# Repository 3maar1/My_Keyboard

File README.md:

# 3maar's Keyboard.
an RGB custom mechanical keyboard with an OLED screen and some custom features.
I made this project because i always wanted to make my stuff by myself and have my name signed on it.

## Custom features:
- signed my name behind
- some sk6812 for better colors since my keyboard is all black.
- an oled screen to give a pretty look 
- some holders from inside the case to ensure having the stability for the PCB.
- and i'm planning to add some of the hack club stickers on the left space when printed.

### -The Schematic
I used kicad with scottokeebs library and wired everything in the schematic. wired some LEDs with each other, the voltage supply and the ground. then made the switches matrix with diodes. it was the simplest thing in this project.

### -The PCB
I used a KLE plugin to arrange the switches and diodes, and manually put the led and the oled. and routed everything together. that was hard a bit but it's done.

### -The 3d Model
I made the 3d model using fusion and added some custom features like signing my name on the back. and made the holes for the socket and the oled. the model is separated to a plate, case, bottom and the pcb inside as a reference. made them all black and designed them to fit together.

### -BOM
this is all the components with their prices and sources
| Item                                     | Price (USD) | Link                                                                                                                                                                                                                                                                                                                                                                                                                                                                                                                                                                                                                                                                                                                                                                                                                                                                                                                |
|------------------------------------------|-------------|---------------------------------------------------------------------------------------------------------------------------------------------------------------------------------------------------------------------------------------------------------------------------------------------------------------------------------------------------------------------------------------------------------------------------------------------------------------------------------------------------------------------------------------------------------------------------------------------------------------------------------------------------------------------------------------------------------------------------------------------------------------------------------------------------------------------------------------------------------------------------------------------------------------------|
| Raspberry Pi Pico                        | 10.27$      | https://mostelectronic.com/shop/arduino-development-boards/raspberry-pi/raspberry-pi-pico/                                                                                                                                                                                                                                                                                                                                                                                                                                                                                                                                                                                                                                                                                                                                                                                                                          |
| Diodes                                   | 0.63$       | https://mostelectronic.com/shop/components/diodes/zener-diode-bzx79-c5v1-6-2-volt/                                                                                                                                                                                                                                                                                                                                                                                                                                                                                                                                                                                                                                                                                                                                                                                                                                  |
| Keyswitches                              | 32.88$      | https://www.amazon.eg/gp/product/B09QGQVQYD/ref=ewc_pr_img_1?smid=A1ZVRGNO5AYLOV&psc=1                                                                                                                                                                                                                                                                                                                                                                                                                                                                                                                                                                                                                                                                                                                                                                                                                              |
| OLED Display 128x64 0.9 Inches           | 3.29$       | https://mostelectronic.com/shop/displays-lcd-7-seg-led/lcd-modules-displays-lcd-7-seg-led/0-96%e2%80%b3-oled-4pin-lcd-led-display-module-i2c-iic-communicate-white-128x64/                                                                                                                                                                                                                                                                                                                                                                                                                                                                                                                                                                                                                                                                                                                                          |
| Keycaps                                  | 7.8$        | https://www.amazon.eg/A101-%D8%B1%D9%8A%D8%AF%D8%B1%D8%A7%D8%AC%D9%88%D9%86-%D8%A7%D9%84%D9%85%D9%81%D8%A7%D8%AA%D9%8A%D8%AD-%D9%84%D9%84%D9%83%D9%8A%D8%A8%D9%88%D8%B1%D8%AF%D8%A7%D8%AA-%D8%A7%D9%84%D9%85%D9%8A%D9%83%D8%A7%D9%86%D9%8A%D9%83%D9%8A%D8%A9/dp/B019OAQ6VI/ref=sr_1_1?crid=131S63DNWPQR6&dib=eyJ2IjoiMSJ9.zIUjY2wUg3Nr9eWWHxwMfdlZPoJ82SGaTR_8OmixACQynGSJOojGDpKWlqtbs5IB6GCVc1rAfDB6EvpbigCdmxsXlxrynCch2fziUpjr7793tyFKOseA_WWf__-g5L1vRob5zpO2BCE7vJej3N2mrVzUkW2OvBvp_q3Jx5KZeFjjB1dGx8bEQDQCwY4ly9DfJHsu265k53HfGW_IibxRO0eW2tv6JjcYAqhP_g4G8SHVFaU4gUwuFmVsNDeqDbZmk1LCvg4wyF9-t-nXhXivgySMUWYcV6g9IOC3sEq67Vg.JFwf40Zm6aGwKnDikG4YgNpKN-pXz8NDLLdcygQKYl0&dib_tag=se&keywords=black%2Bkeycaps&qid=1753918745&sprefix=black%2Bkeycaps%2Caps%2C177&sr=8-1&th=1                                                                                                                                |
| Solderig Wire                            | 1.54$       | https://mostelectronic.com/shop/tools/soldering-desoldering/solder-wire-singapore-25g-0-6mm-70-30-singapore/                                                                                                                                                                                                                                                                                                                                                                                                                                                                                                                                                                                                                                                                                                                                                                                                        |
| Soldering Iron Tips                      | 1.34$       | https://mostelectronic.com/shop/tools/soldering-desoldering/soldering-iron-station-tips-5pcs/                                                                                                                                                                                                                                                                                                                                                                                                                                                                                                                                                                                                                                                                                                                                                                                                                       |
| ""Most Electronics""  shop shipping fees | 1.54$       | Raspberry Pi Pico + Diodes + OLED Display + Soldering Wire + Soldering Iron Tips                                                                                                                                                                                                                                                                                                                                                                                                                                                                                                                                                                                                                                                                                                                                                                                                                                    |
| ""Amazon"" shipping fees                 | Free        | Keyswitches + Keycaps                                                                                                                                                                                                                                                                                                                                                                                                                                                                                                                                                                                                                                                                                                                                                                                                                                                                                               |
| ""JLCPCB"" Printing with shipping fees   | 18.20$      | PCB printing                                                                                                                                                                                                                                                                                                                                                                                                                                                                                                                                                                                                                                                                                                                                                                                                                                                                                                        |
| Glue                                     | 2.88$       | https://www.amazon.eg/%D9%85%D8%AA%D8%B9%D8%AF%D8%AF-%D8%A7%D9%84%D8%A7%D8%B3%D8%AA%D8%AE%D8%AF%D8%A7%D9%85%D8%A7%D8%AA-%D9%85%D9%88%D8%AF%D9%8A%D9%84-%D8%A7%D9%83%D9%81%D9%8A%D9%83%D8%B3%D8%8C-200/dp/B07MCQWCQV/ref=sr_1_2_sspa?adgrpid=127622644738&dib=eyJ2IjoiMSJ9.Rf2A_6F5nfZcD1RmeMcJpFQSRa30viTUIw-x_MyzMeJ1AiD2L1bPRZDLmLnoLul1KYhFy_QSjzfgK-treEua1nli70iMJfrofePkCMu0A3bZbqZghVaXefjHYOZD614siKel_O5CUiHmfKKwenZMTNJF8zwEuxDhdqLnKAa5aG3003BbwqbkiEX-bVfT4IPh4PeIABdhXn1ufM_4d2KFKYwFknr8jXtUKS1VHAnI68jTP1qhWldfy3qOXI_vLdi32eYgrURm7qCcVfkfI7C9uzjB9BGFt9hC48oXCFNjeI0.VBGY9t3wS5zmli7nohzKlfATAdpz18BlYceCK70TaR8&dib_tag=se&hvadid=669800591195&hvdev=c&hvlocphy=9195686&hvnetw=g&hvqmt=e&hvrand=10375869494463082146&hvtargid=kwd-299904148450&hydadcr=12482_2432580&keywords=plastic+glue&mcid=4f501f1c5bf83f238f209bec23c2ac0c&qid=1753884036&sr=8-2-spons&sp_csd=d2lkZ2V0TmFtZT1zcF9hdGY&psc=1 |
| ""Printfy3d"" Printing with shipping fee | 28.61$      | Case Printing                                                                                                                                                                                                                                                                                                                                                                                                                                                                                                                                                                                                                                                                                                                                                                                                                                                                                                       |
| LED SK6812 mini                          | 11$         | https://ar.aliexpress.com/item/1005007988694935.html?spm=a2g0o.productlist.main.3.5396FIQ7FIQ7cv&algo_pvid=5222bd69-e636-46e4-9d6c-1b32006ccb38&algo_exp_id=5222bd69-e636-46e4-9d6c-1b32006ccb38-2&pdp_ext_f=%7B%22order%22%3A%2215%22%2C%22eval%22%3A%221%22%7D&pdp_npi=4%40dis%21EGP%21473.83%21416.97%21%21%2163.50%2155.88%21%400b1bf20817539189737827890e438d%2112000043173268003%21sea%21EG%216193735018%21ABX&curPageLogUid=JGMNxlhrKvmw&utparam-url=scene%3Asearch%7Cquery_from%3A&_gl=1*15xcswx*_gcl_au*MjA4Njg5MDI1NC4xNzUzNjI3MzIx*_ga*MTA2MjY3MzU0NS4xNzUzNjI3MzIx*_ga_VED1YSGNC7*czE3NTM5MTg5NTckbzMkZzEkdDE3NTM5MTg5NjkkajQ4JGwwJGgw                                                                                                                                                                                                                                                                  |
| stabilizers                              | 2.5$        | https://ar.aliexpress.com/item/1005003683101493.html?spm=a2g0o.productlist.main.6.2e42f1cUf1cUua&algo_pvid=90b15ee9-c0b0-4055-ba05-897a77aaf90d&algo_exp_id=90b15ee9-c0b0-4055-ba05-897a77aaf90d-5&pdp_ext_f=%7B%22order%22%3A%2252%22%2C%22eval%22%3A%221%22%7D&pdp_npi=4%40dis%21EGP%21642.25%21513.58%21%21%2111.98%219.58%21%400b1bf20817539919216313288eb415%2112000030083766088%21sea%21EG%216193735018%21ABX&curPageLogUid=kdGEnz5bNc6d&utparam-url=scene%3Asearch%7Cquery_from%3A&_gl=1*pa89kx*_gcl_au*MjA4Njg5MDI1NC4xNzUzNjI3MzIx*_ga*MTA2MjY3MzU0NS4xNzUzNjI3MzIx*_ga_VED1YSGNC7*czE3NTM5OTE3MjQkbzQkZzEkdDE3NTM5OTE5MTgkajUkbDAkaDA.                                                                                                                                                                                                                                                                    |
| soldering paste flux                     | 1.22$       | https://mostelectronic.com/shop/tools/soldering-desoldering/joker-soldering-paste-flux-for-multi-purpose-50g/                                                                                                                                                                                                                                                                                                                                                                                                                                                                                                                                                                                                                                                                                                                                                                                                       |
| Total                                    | 124$        |                                                                                                                                                                                                                                                                                                                                                                                                                                                                                                                                                                                                                                                                                                                                                                                                                                                                                                                     |

here is the link for the spread sheet:https://stemschools-my.sharepoint.com/:x:/g/personal/ammar_1024104_stemoctober_moe_edu_eg/EaMfzBkgDNVCjZ2IeJW4RrMBYXwM8-TcE8Ny9vNTQ7Igzg?e=zn2DD8&nav=MTVfezIzNEYzOTM1LUEyREEtNEE3NC05Mzc0LTE0MzFFQzI2RUU0MH0

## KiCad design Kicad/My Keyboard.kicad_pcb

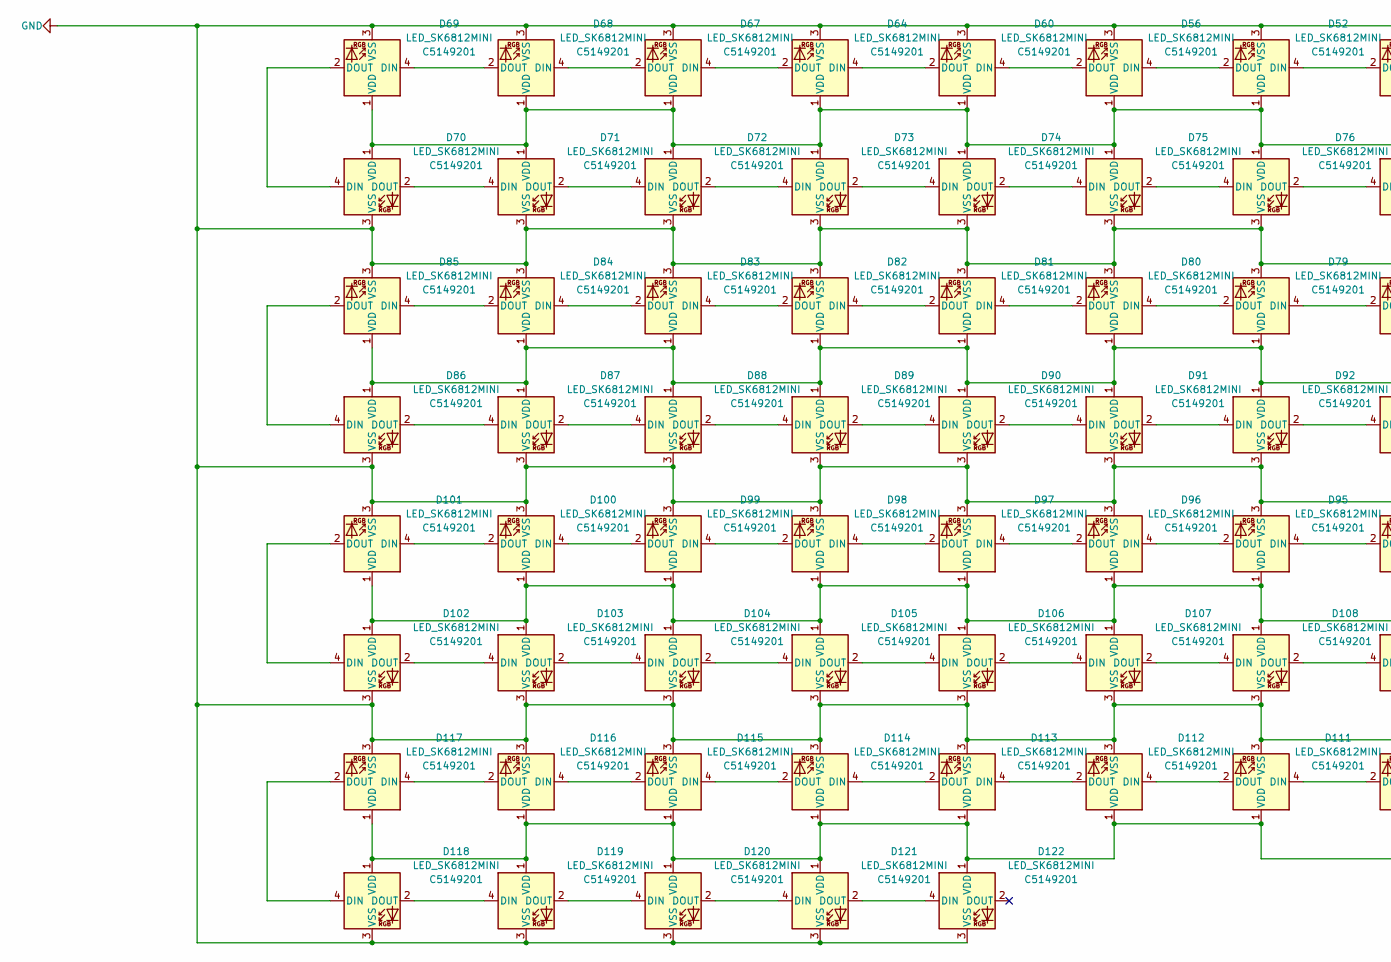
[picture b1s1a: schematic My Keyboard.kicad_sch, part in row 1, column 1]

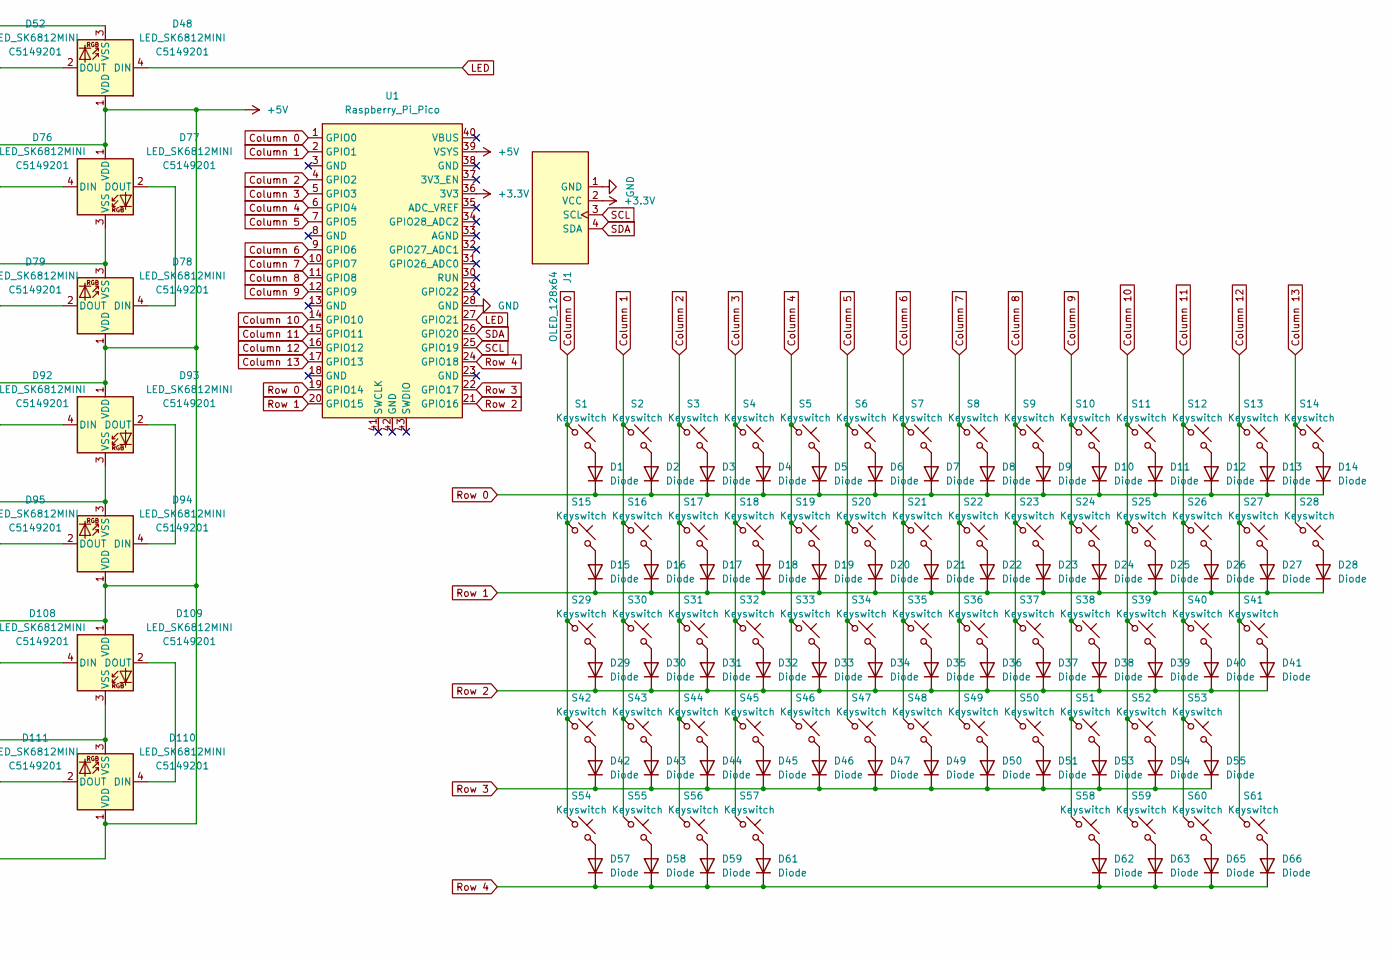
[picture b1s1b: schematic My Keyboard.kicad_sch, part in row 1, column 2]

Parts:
D1, D2, D3, D4, D5, D6, D7, D8, D9, D10, D11, D12, D13, D14, D15, D16, D17, D18, D19, D20, D21, D22, D23, D24, D25, D26, D27, D28, D29, D30, D31, D32, D33, D34, D35, D36, D37, D38, D39, D40, D41, D42, D43, D44, D45, D46, D47, D49, D50, D51, D53, D54, D55, D57, D58, D59, D61, D62, D63, D65, D66: Diode; Diode_DO-35
D48, D52, D56, D60, D64, D67, D68, D69, D70, D71, D72, D73, D74, D75, D76, D77, D78, D79, D80, D81, D82, D83, D84, D85, D86, D87, D88, D89, D90, D91, D92, D93, D94, D95, D96, D97, D98, D99, D100, D101, D102, D103, D104, D105, D106, D107, D108, D109, D110, D111, D112, D113, D114, D115, D116, D117, D118, D119, D120, D121, D122: LED_SK6812MINI; LCSC C5149201
J1: OLED_128x64
S1, S2, S3, S4, S5, S6, S7, S8, S9, S10, S11, S12, S13, S14, S15, S16, S17, S18, S19, S20, S21, S22, S23, S24, S25, S26, S27, S28, S29, S30, S31, S32, S33, S34, S35, S36, S37, S38, S39, S40, S41, S42, S43, S44, S45, S46, S47, S48, S49, S50, S51, S52, S53, S54, S55, S56, S57, S58, S59, S60, S61: Keyswitch; SW_Cherry_MX_1.00u_PCB
U1: Raspberry_Pi_Pico

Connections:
+3.3V: J1.2 (VCC), U1.36 (3V3), U1.40 (VBUS)
+5V: D48.1 (VDD), D52.1 (VDD), D56.1 (VDD), D60.1 (VDD), D64.1 (VDD), D67.1 (VDD), D68.1 (VDD), D69.1 (VDD), D70.1 (VDD), D71.1 (VDD), D72.1 (VDD), D73.1 (VDD), D74.1 (VDD), D75.1 (VDD), D76.1 (VDD), D77.1 (VDD), D78.1 (VDD), D79.1 (VDD), D80.1 (VDD), D81.1 (VDD), D82.1 (VDD), D83.1 (VDD), D84.1 (VDD), D85.1 (VDD), D86.1 (VDD), D87.1 (VDD), D88.1 (VDD), D89.1 (VDD), D90.1 (VDD), D91.1 (VDD), D92.1 (VDD), D93.1 (VDD), D94.1 (VDD), D95.1 (VDD), D96.1 (VDD), D97.1 (VDD), D98.1 (VDD), D99.1 (VDD), D100.1 (VDD), D101.1 (VDD), D102.1 (VDD), D103.1 (VDD), D104.1 (VDD), D105.1 (VDD), D106.1 (VDD), D107.1 (VDD), D108.1 (VDD), D109.1 (VDD), D110.1 (VDD), D111.1 (VDD), D112.1 (VDD), D113.1 (VDD), D114.1 (VDD), D115.1 (VDD), D116.1 (VDD), D117.1 (VDD), D118.1 (VDD), D119.1 (VDD), D120.1 (VDD), D121.1 (VDD), D122.1 (VDD), U1.39 (VSYS)
Column 0: S1.1, S15.1, S29.1, S42.1, S54.1, U1.1 (GPIO0)
Column 1: S2.1, S16.1, S30.1, S43.1, S55.1, U1.2 (GPIO1)
Column 2: S3.1, S17.1, S31.1, S44.1, S56.1, U1.4 (GPIO2)
Column 3: S4.1, S18.1, S32.1, S45.1, S57.1, U1.5 (GPIO3)
Column 4: S5.1, S19.1, S33.1, S46.1, U1.6 (GPIO4)
Column 5: S6.1, S20.1, S34.1, S47.1, U1.7 (GPIO5)
Column 6: S7.1, S21.1, S35.1, S48.1, U1.9 (GPIO6)
Column 7: S8.1, S22.1, S36.1, S49.1, U1.10 (GPIO7)
Column 8: S9.1, S23.1, S37.1, S50.1, U1.11 (GPIO8)
Column 9: S10.1, S24.1, S38.1, S51.1, S58.1, U1.12 (GPIO9)
Column 10: S11.1, S25.1, S39.1, S52.1, S59.1, U1.14 (GPIO10)
Column 11: S12.1, S26.1, S40.1, S53.1, S60.1, U1.15 (GPIO11)
Column 12: S13.1, S27.1, S41.1, S61.1, U1.16 (GPIO12)
Column 13: S14.1, S28.1, U1.17 (GPIO13)
GND: D48.3 (VSS), D52.3 (VSS), D56.3 (VSS), D60.3 (VSS), D64.3 (VSS), D67.3 (VSS), D68.3 (VSS), D69.3 (VSS), D70.3 (VSS), D71.3 (VSS), D72.3 (VSS), D73.3 (VSS), D74.3 (VSS), D75.3 (VSS), D76.3 (VSS), D77.3 (VSS), D78.3 (VSS), D79.3 (VSS), D80.3 (VSS), D81.3 (VSS), D82.3 (VSS), D83.3 (VSS), D84.3 (VSS), D85.3 (VSS), D86.3 (VSS), D87.3 (VSS), D88.3 (VSS), D89.3 (VSS), D90.3 (VSS), D91.3 (VSS), D92.3 (VSS), D93.3 (VSS), D94.3 (VSS), D95.3 (VSS), D96.3 (VSS), D97.3 (VSS), D98.3 (VSS), D99.3 (VSS), D100.3 (VSS), D101.3 (VSS), D102.3 (VSS), D103.3 (VSS), D104.3 (VSS), D105.3 (VSS), D106.3 (VSS), D107.3 (VSS), D108.3 (VSS), D109.3 (VSS), D110.3 (VSS), D111.3 (VSS), D112.3 (VSS), D113.3 (VSS), D114.3 (VSS), D115.3 (VSS), D116.3 (VSS), D117.3 (VSS), D118.3 (VSS), D119.3 (VSS), D120.3 (VSS), D121.3 (VSS), D122.3 (VSS), J1.1 (GND), U1.28 (GND)
LED: D48.4 (DIN), U1.27 (GPIO21)
unnamed: D1.2 (A), S1.2
unnamed: D2.2 (A), S2.2
unnamed: D3.2 (A), S3.2
unnamed: D4.2 (A), S4.2
unnamed: D5.2 (A), S5.2
unnamed: D6.2 (A), S6.2
unnamed: D7.2 (A), S7.2
unnamed: D8.2 (A), S8.2
unnamed: D9.2 (A), S9.2
unnamed: D10.2 (A), S10.2
unnamed: D11.2 (A), S11.2
unnamed: D12.2 (A), S12.2
unnamed: D13.2 (A), S13.2
unnamed: D14.2 (A), S14.2
unnamed: D15.2 (A), S15.2
unnamed: D16.2 (A), S16.2
unnamed: D17.2 (A), S17.2
unnamed: D18.2 (A), S18.2
unnamed: D19.2 (A), S19.2
unnamed: D20.2 (A), S20.2
unnamed: D21.2 (A), S21.2
unnamed: D22.2 (A), S22.2
unnamed: D23.2 (A), S23.2
unnamed: D24.2 (A), S24.2
unnamed: D25.2 (A), S25.2
unnamed: D26.2 (A), S26.2
unnamed: D27.2 (A), S27.2
unnamed: D28.2 (A), S28.2
unnamed: D29.2 (A), S29.2
unnamed: D30.2 (A), S30.2
unnamed: D31.2 (A), S31.2
unnamed: D32.2 (A), S32.2
unnamed: D33.2 (A), S33.2
unnamed: D34.2 (A), S34.2
unnamed: D35.2 (A), S35.2
unnamed: D36.2 (A), S36.2
unnamed: D37.2 (A), S37.2
unnamed: D38.2 (A), S38.2
unnamed: D39.2 (A), S39.2
unnamed: D40.2 (A), S40.2
unnamed: D41.2 (A), S41.2
unnamed: D42.2 (A), S42.2
unnamed: D43.2 (A), S43.2
unnamed: D44.2 (A), S44.2
unnamed: D45.2 (A), S45.2
unnamed: D46.2 (A), S46.2
unnamed: D47.2 (A), S47.2
unnamed: D48.2 (DOUT), D52.4 (DIN)
unnamed: D49.2 (A), S48.2
unnamed: D50.2 (A), S49.2
unnamed: D51.2 (A), S50.2
unnamed: D52.2 (DOUT), D56.4 (DIN)
unnamed: D53.2 (A), S51.2
unnamed: D54.2 (A), S52.2
unnamed: D55.2 (A), S53.2
unnamed: D56.2 (DOUT), D60.4 (DIN)
unnamed: D57.2 (A), S54.2
unnamed: D58.2 (A), S55.2
unnamed: D59.2 (A), S56.2
unnamed: D60.2 (DOUT), D64.4 (DIN)
unnamed: D61.2 (A), S57.2
unnamed: D62.2 (A), S58.2
unnamed: D63.2 (A), S59.2
unnamed: D64.2 (DOUT), D67.4 (DIN)
unnamed: D65.2 (A), S60.2
unnamed: D66.2 (A), S61.2
unnamed: D67.2 (DOUT), D68.4 (DIN)
unnamed: D68.2 (DOUT), D69.4 (DIN)
unnamed: D69.2 (DOUT), D70.4 (DIN)
unnamed: D70.2 (DOUT), D71.4 (DIN)
unnamed: D71.2 (DOUT), D72.4 (DIN)
unnamed: D72.2 (DOUT), D73.4 (DIN)
unnamed: D73.2 (DOUT), D74.4 (DIN)
unnamed: D74.2 (DOUT), D75.4 (DIN)
unnamed: D75.2 (DOUT), D76.4 (DIN)
unnamed: D76.2 (DOUT), D77.4 (DIN)
unnamed: D77.2 (DOUT), D78.4 (DIN)
unnamed: D78.2 (DOUT), D79.4 (DIN)
unnamed: D79.2 (DOUT), D80.4 (DIN)
unnamed: D80.2 (DOUT), D81.4 (DIN)
unnamed: D81.2 (DOUT), D82.4 (DIN)
unnamed: D82.2 (DOUT), D83.4 (DIN)
unnamed: D83.2 (DOUT), D84.4 (DIN)
unnamed: D84.2 (DOUT), D85.4 (DIN)
unnamed: D85.2 (DOUT), D86.4 (DIN)
unnamed: D86.2 (DOUT), D87.4 (DIN)
unnamed: D87.2 (DOUT), D88.4 (DIN)
unnamed: D88.2 (DOUT), D89.4 (DIN)
unnamed: D89.2 (DOUT), D90.4 (DIN)
unnamed: D90.2 (DOUT), D91.4 (DIN)
unnamed: D91.2 (DOUT), D92.4 (DIN)
unnamed: D92.2 (DOUT), D93.4 (DIN)
unnamed: D93.2 (DOUT), D94.4 (DIN)
unnamed: D94.2 (DOUT), D95.4 (DIN)
unnamed: D95.2 (DOUT), D96.4 (DIN)
unnamed: D96.2 (DOUT), D97.4 (DIN)
unnamed: D97.2 (DOUT), D98.4 (DIN)
unnamed: D98.2 (DOUT), D99.4 (DIN)
unnamed: D99.2 (DOUT), D100.4 (DIN)
unnamed: D100.2 (DOUT), D101.4 (DIN)
unnamed: D101.2 (DOUT), D102.4 (DIN)
unnamed: D102.2 (DOUT), D103.4 (DIN)
unnamed: D103.2 (DOUT), D104.4 (DIN)
unnamed: D104.2 (DOUT), D105.4 (DIN)
unnamed: D105.2 (DOUT), D106.4 (DIN)
unnamed: D106.2 (DOUT), D107.4 (DIN)
unnamed: D107.2 (DOUT), D108.4 (DIN)
unnamed: D108.2 (DOUT), D109.4 (DIN)
unnamed: D109.2 (DOUT), D110.4 (DIN)
unnamed: D110.2 (DOUT), D111.4 (DIN)
unnamed: D111.2 (DOUT), D112.4 (DIN)
unnamed: D112.2 (DOUT), D113.4 (DIN)
unnamed: D113.2 (DOUT), D114.4 (DIN)
unnamed: D114.2 (DOUT), D115.4 (DIN)
unnamed: D115.2 (DOUT), D116.4 (DIN)
unnamed: D116.2 (DOUT), D117.4 (DIN)
unnamed: D117.2 (DOUT), D118.4 (DIN)
unnamed: D118.2 (DOUT), D119.4 (DIN)
unnamed: D119.2 (DOUT), D120.4 (DIN)
unnamed: D120.2 (DOUT), D121.4 (DIN)
unnamed: D121.2 (DOUT), D122.4 (DIN)
Row 0: D1.1 (K), D2.1 (K), D3.1 (K), D4.1 (K), D5.1 (K), D6.1 (K), D7.1 (K), D8.1 (K), D9.1 (K), D10.1 (K), D11.1 (K), D12.1 (K), D13.1 (K), D14.1 (K), U1.19 (GPIO14)
Row 1: D15.1 (K), D16.1 (K), D17.1 (K), D18.1 (K), D19.1 (K), D20.1 (K), D21.1 (K), D22.1 (K), D23.1 (K), D24.1 (K), D25.1 (K), D26.1 (K), D27.1 (K), D28.1 (K), U1.20 (GPIO15)
Row 2: D29.1 (K), D30.1 (K), D31.1 (K), D32.1 (K), D33.1 (K), D34.1 (K), D35.1 (K), D36.1 (K), D37.1 (K), D38.1 (K), D39.1 (K), D40.1 (K), D41.1 (K), U1.21 (GPIO16)
Row 3: D42.1 (K), D43.1 (K), D44.1 (K), D45.1 (K), D46.1 (K), D47.1 (K), D49.1 (K), D50.1 (K), D51.1 (K), D53.1 (K), D54.1 (K), D55.1 (K), U1.22 (GPIO17)
Row 4: D57.1 (K), D58.1 (K), D59.1 (K), D61.1 (K), D62.1 (K), D63.1 (K), D65.1 (K), D66.1 (K), U1.24 (GPIO18)
SCL: J1.3 (SCL), U1.25 (GPIO19)
SDA: J1.4 (SDA), U1.26 (GPIO20)

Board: 2 copper layers, 185 parts (61 on the bottom side), 146 nets, no tracks yet.

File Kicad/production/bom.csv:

Designator,Footprint,Quantity,Value,LCSC Part #
"D1, D10, D11, D12, D13, D14, D15, D16, D17, D18, D19, D2, D20, D21, D22, D23, D24, D25, D26, D27, D28, D29, D3, D30, D31, D32, D33, D34, D35, D36, D37, D38, D39, D4, D40, D41, D42, D43, D44, D45, D46, D47, D49, D5, D50, D51, D53, D54, D55, D57, D58, D59, D6, D61, D62, D63, D65, D66, D7, D8, D9",Diode_DO-35,61,Diode,
"D100, D101, D102, D103, D104, D105, D106, D107, D108, D109, D110, D111, D112, D113, D114, D115, D116, D117, D118, D119, D120, D121, D122, D48, D52, D56, D60, D64, D67, D68, D69, D70, D71, D72, D73, D74, D75, D76, D77, D78, D79, D80, D81, D82, D83, D84, D85, D86, D87, D88, D89, D90, D91, D92, D93, D94, D95, D96, D97, D98, D99",LED_SK6812MINI,61,LED_SK6812MINI,C5149201
J1,OLED_128x64,1,OLED_128x64,
"S1, S10, S11, S12, S13, S14, S15, S16, S17, S18, S19, S2, S20, S21, S22, S23, S24, S25, S26, S27, S28, S29, S3, S30, S31, S32, S33, S34, S35, S36, S37, S38, S39, S4, S40, S41, S42, S43, S44, S45, S46, S47, S48, S49, S5, S50, S51, S52, S53, S54, S55, S56, S57, S58, S59, S6, S60, S61, S7, S8, S9",MX_PCB_1.00u,61,Keyswitch,
U1,Raspberry_Pi_Pico,1,Raspberry_Pi_Pico,

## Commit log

2025-07-23 Pcb and Schematic update
2025-07-26 some changes
2025-07-26 firmware
2025-07-27 final touches.
2025-07-30 Finally!
2025-07-30 Done
2025-07-30 some missing things..
